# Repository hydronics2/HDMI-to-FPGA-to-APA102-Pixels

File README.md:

# Oregon Museum of Science & Industry (OMSI) - giant LED wall

132 APA102 LED panels, 680 pixels per panel, 90,000 pixels, 300sqft, 4 Spartan 6 Mojo FPGAs
[hackaday.io](https://hackaday.io/project/163657-hdmi-to-fpga-to-apa102)

LED Wall at Oregon Museum of Science & Industry(OMSI): https://photos.app.goo.gl/8hZoa7y9F9Lsg7Md9 (animation credit to [yassi @ openprocessing.org](https://www.openprocessing.org/user/65007))

The creative director wanted to put the LED display behind a wood grain pattern similar to the wall at Microsoft HQ. When the LEDs are off the visitor sees a seemless, unobtrusive wall. To make the LEDs pop behind the wood grain graphic we used a very brigtht APA102.

The resolution is about 24' wide by 14' high. That's 408 pixels wide 220 pixels tall. Not quite VGA.

The FPGA's boards are Spartan 6 on a Mojo development platform: https://alchitry.com/ The wall is broken down into 4 sections for 4 Mojo's and each Mojo receives the same HDMI signal but only grabs pixels for the section of LEDs it controls.

Alchitry has an HDMI shield for the Mojo and the FPGA code is written in their programming environment in Lucid a form of Verilog. It's great for beginners. This was my first FPGA project.

The HDMI signal is decoded and pixels arranged for each panel in local memory (RAM). There is just enough memory to save about 30% of the pixels so it takes 3 passes to arrange and output all the pixels... 60HZ / 3 gives us 20 frames per second. Thanks to [David Hulton](https://www.meetup.com/PNW-FPGA-Hackers-Meetup/) and Devin Boyer for sharing their mad FPGA memory tricks at [Toorcamp 2018](https://toorcamp.toorcon.net/).

The SPI clock speed for writing to the APA102 also has speed limits as we 'race the beam.' Here's a great article by [Paul Stoffregen (teensy)](https://www.pjrc.com/why-apa102-leds-have-trouble-at-24-mhz/) on these limits. The gist is the clock signals start to deteriorate between the pixels. For the 680 LEDs in our panel, I was able to write confidently at 6.25 MHZ. You can see how this clock signal is generated in any one of the 32 SPI modules in the source file under Mojo.

The FPGA generates an SPI clock and data signal to each LED panel. The signals are immediately fed from a simple shield to another custom PCB with [RS485 transmitters](https://www.digikey.com/product-detail/en/texas-instruments/AM26LV31EIDR/296-24690-1-ND/2092512) shown above. The transmitter chips output differential signal pairs that pass easily in ethernet cords over 20-30 feet to each panel location. At the LED panel, the signals are received with [transceiver](https://www.digikey.com/product-detail/en/maxlinear-inc/SP485EN-L-TR/1016-1829-1-ND/3586546) chips bacck into clock and data lines and connected to their respective LED panel. This custom PCB also has a small DC-DC voltage transformers that take a 45VDC buss down to the 5V required for the LEDs.  The below PCB has tranceiver chips and three DC-DC transformers serving 3 LED panels. Thanks to Tom Moxon with [Pattern Agents](http://patternagents.com/) for help designing this circuit.

The led panels themselves are little more than strip LEDs that have been connected together.  We had them customized for our particular geometry by the [supplier](https://www.aliexpress.com/store/product/30-40-pixels-RGB-full-color-WS2812B-Flexible-LED-Pixel-Panel-Light-DC5V/701799_32601735218.html).

Mojo HDMI Shield: https://embeddedmicro.com/products/hdmi-shield

This design builds off of a lucid module example for decoding HDMI signals: https://embeddedmicro.com/blogs/tutorials/hdmi-shield-basics

Thanks to Walsh Construction for making it look easy to hang giant pieces of Acrylic exactly on target.

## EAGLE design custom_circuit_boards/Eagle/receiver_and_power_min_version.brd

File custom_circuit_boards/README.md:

# Custom Circuit Boards

We used 3 types of circuit boards.
* A simple shield for the mojo that broke out all the SPI and Clock signals to the LED panels.
* A transmitter board that sends the clock and data signal out over RS485
* A receiver board that has transceiver chips, takes the signals 

Mojo Shield has all the pins broken out. We needed 33 SPI Data pins and the clock pin was shared across all the Panels.  The pins are broken out to 5.08mm phoenix connectors. The HDMI shield fits on the Mojo and this shield connects ontop of the HDMI shield. [Oshpark](https://oshpark.com/shared_projects/AGi8q5pp)

The transmitter board takes two SPI signals (Clock and Data) and passes the signals through an RS485 transmitter chip. The differential signals are routed to an ethernet jack. This board could have been integrated into the Mojo shield to reduce noise but my disigning, programming, prototyping, and installing timelines compressed the schedule and I had to learn as I went. [Oshpark](https://oshpark.com/shared_projects/nhExJAWv)

* transmitter chip: Texas Instrument AM27LV31 296-24690-1-ND
* RJ45 ethernet jack: 380-1316-5-ND
* 

The receiver board receives RS485 signals via a RJ485 ethernet jack. Converts the two differential pairs back into clock and data SPI signals and connects to one LED panel. The board also has a DC-to-DC converter that takes 45V to 5V to supply to the LED panel. I did not put the TVS protection diodes on the boards but added them on just the last few boards I made when troubleshooting noise issues.  Also, in addition to the 120ohm termination resistors on the RS485 bus, the original boards have 4.7k pullup and pulldown resistors on the bus. Modern RS485 chips have whats called "failsafe" against idle(no Data) conditions that these resistors are meant to deter.... so I left them out of these last few single signal boards shown here. [Oshpark](https://oshpark.com/shared_projects/qSwC1Fum)

* Trnsceiver Chip: SP485EN, 1016-1829-1-ND
* RJ45 Ethernet Jack: 380-1316-5-ND
* DC-DC converter - PYB20-Q48-S5

* [Mojo Development Board](https://alchitry.com/products/mojo-v3)
* [HDMI Shield](https://alchitry.com/products/hdmi-shield)
* [RS485 transmitter chips](https://www.digikey.com/product-detail/en/texas-instruments/AM26LV31EIDR/296-24690-1-ND/2092512) shown above.
* [RS485 transceiver chips](https://www.digikey.com/product-detail/en/maxlinear-inc/SP485EN-L-TR/1016-1829-1-ND/3586546) chips
* [Mojo HDMI Shield](https://embeddedmicro.com/products/hdmi-shield)

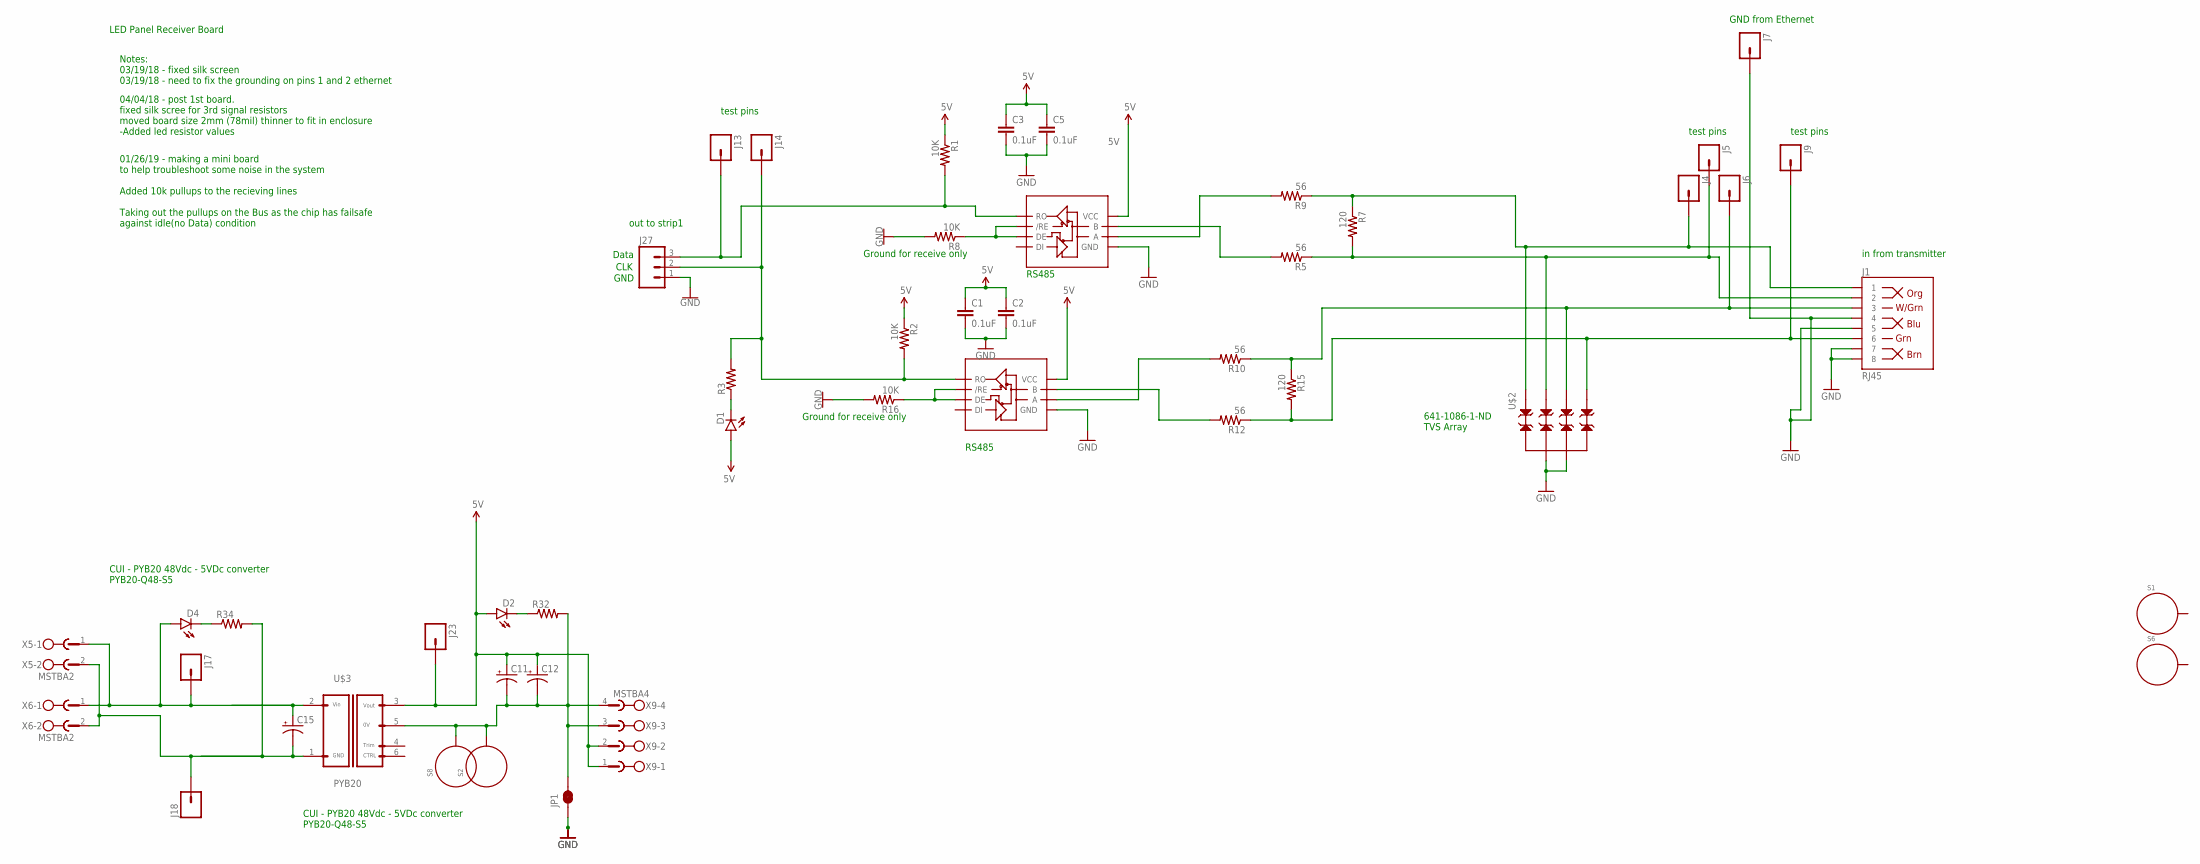
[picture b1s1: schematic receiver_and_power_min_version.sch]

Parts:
C1, C2, C3, C5: 0.1uF; 0805
C11, C12, C15: CAP_POLPTH4; CPOL-RADIAL-1000UF-25V
D1, D2, D4: LED3MM
J1: RJ45; RJ45-8
J4, J5, J6, J7, J9, J13, J14, J17, J18, J23: M01PTH; 1X01
J27: M03SCREW; SCREWTERMINAL-3.5MM-3
JP1: JUMPER-PAD-2-NC_BY_TRACE; PAD-JUMPER-2-NC_BY_TRACE_YES_SILK
R1, R2, R8, R16: 10K; 0805
R3: RESISTOR0805-RES; 0805
R5, R9, R10, R12: 56; 0805
R7, R15: 120; 0805
R32, R34: RESISTORPTH-1/4W; AXIAL-0.4
S1, S2, S6, S8: STANDOFF_ELECTRICAL5-32; STANDOFF_ELECTRICAL_5_32
U1, U2: ST1480ACSOIC; SO08
U$2: TVS_ARRAY; SOT26
U$3: PYB20; CUI_PYB20_PCB_DC_DC
X5, X6: MSTBA2
X9: MSTBA4

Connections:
5GND1: C11.2 (-), C12.2 (-), JP1.2, R32.P$2 (2), S2.P1, S8.P1, U$3.5 (0V), X9.3, X9.4
5V: C1.1, C2.1, C3.1, C5.1, C11.1 (+), C12.1 (+), D1.A, D2.A, J23.1, R1.1, R2.1, U1.8 (VCC), U2.8 (VCC), U$3.3 (V+), X9.1, X9.2
48GND: C15.-, J18.1, R34.P$2 (2), U$3.1 (GND1), X5.2, X6.2
48V: C15.+, D4.A, J17.1, U$3.2 (VIN), X5.1, X6.1
A: R9.2, U1.6 (A)
A1: R10.2, U2.6 (A)
AO: J1.1, J4.1, R7.1, R9.1, U$2.1
AO1: J1.3, J6.1, R10.1, R15.1, U$2.4
B: R5.2, U1.7 (B)
B1: R12.2, U2.7 (B)
BO: J1.2, J5.1, R5.1, R7.2, U$2.3
BO1: J1.6, J9.1, R12.1, R15.2, U$2.6
DE: R8.1, U1.2 (/RE), U1.3 (DE)
DE1: R16.1, U2.2 (/RE), U2.3 (DE)
GND: C1.2, C2.2, C3.2, C5.2, J1.4, J1.5, J1.7, J1.8, J7.1, J27.1, JP1.1, R8.2, R16.2, U1.5 (GND), U2.5 (GND), U$2.2, U$2.5
unnamed: D1.K (C), R3.1
unnamed: D4.K (C), R34.P$1 (1)
unnamed: D2.K (C), R32.P$1 (1)
RXD: J13.1, J27.3, R1.2, U1.1 (RO)
RXD1: J14.1, J27.2, R2.2, R3.2, U2.1 (RO)

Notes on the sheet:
in from transmitter
test pins
Ground for receive only
out to strip1
LED Panel Receiver Board
GND from Ethernet
RS485
Notes: 03/19/18 - fixed silk screen 03/19/18 - need to fix the grounding on pins 1 and 2 ethernet
GND
CLK
Data
CUI - PYB20 48Vdc - 5VDc converter PYB20-Q48-S5
04/04/18 - post 1st board. fixed silk scree for 3rd signal resistors moved board size 2mm (78mil) thinner to fit in enclosure -Added led resistor values
01/26/19 - making a mini board to help troubleshoot some noise in the system Added 10k pullups to the recieving lines Taking out the pullups on the Bus as the chip has failsafe against idle(no Data) condition
641-1086-1-ND TVS Array

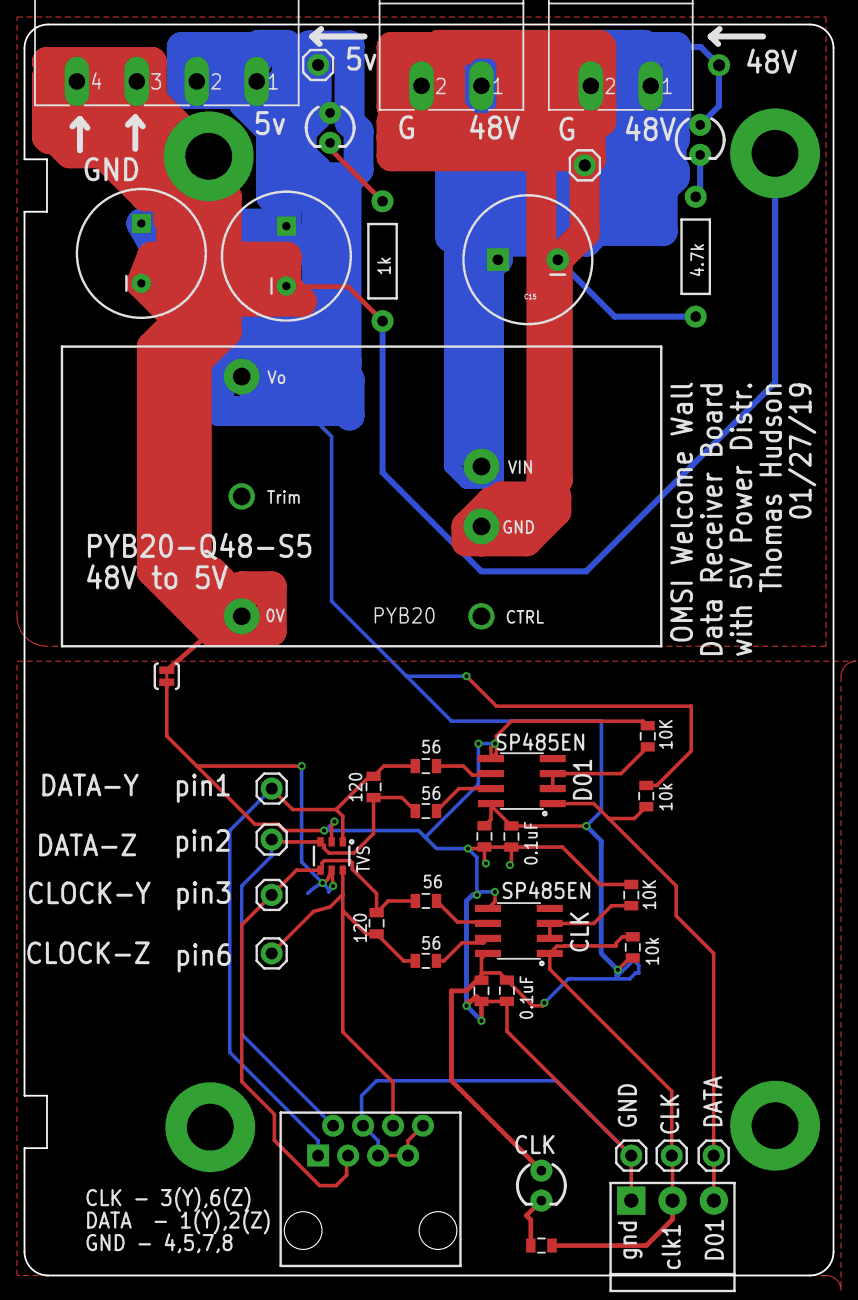
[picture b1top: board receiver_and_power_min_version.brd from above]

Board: 2 copper layers, 68.6 x 106.0 mm, 47 parts (1 on the bottom side), 20 nets.

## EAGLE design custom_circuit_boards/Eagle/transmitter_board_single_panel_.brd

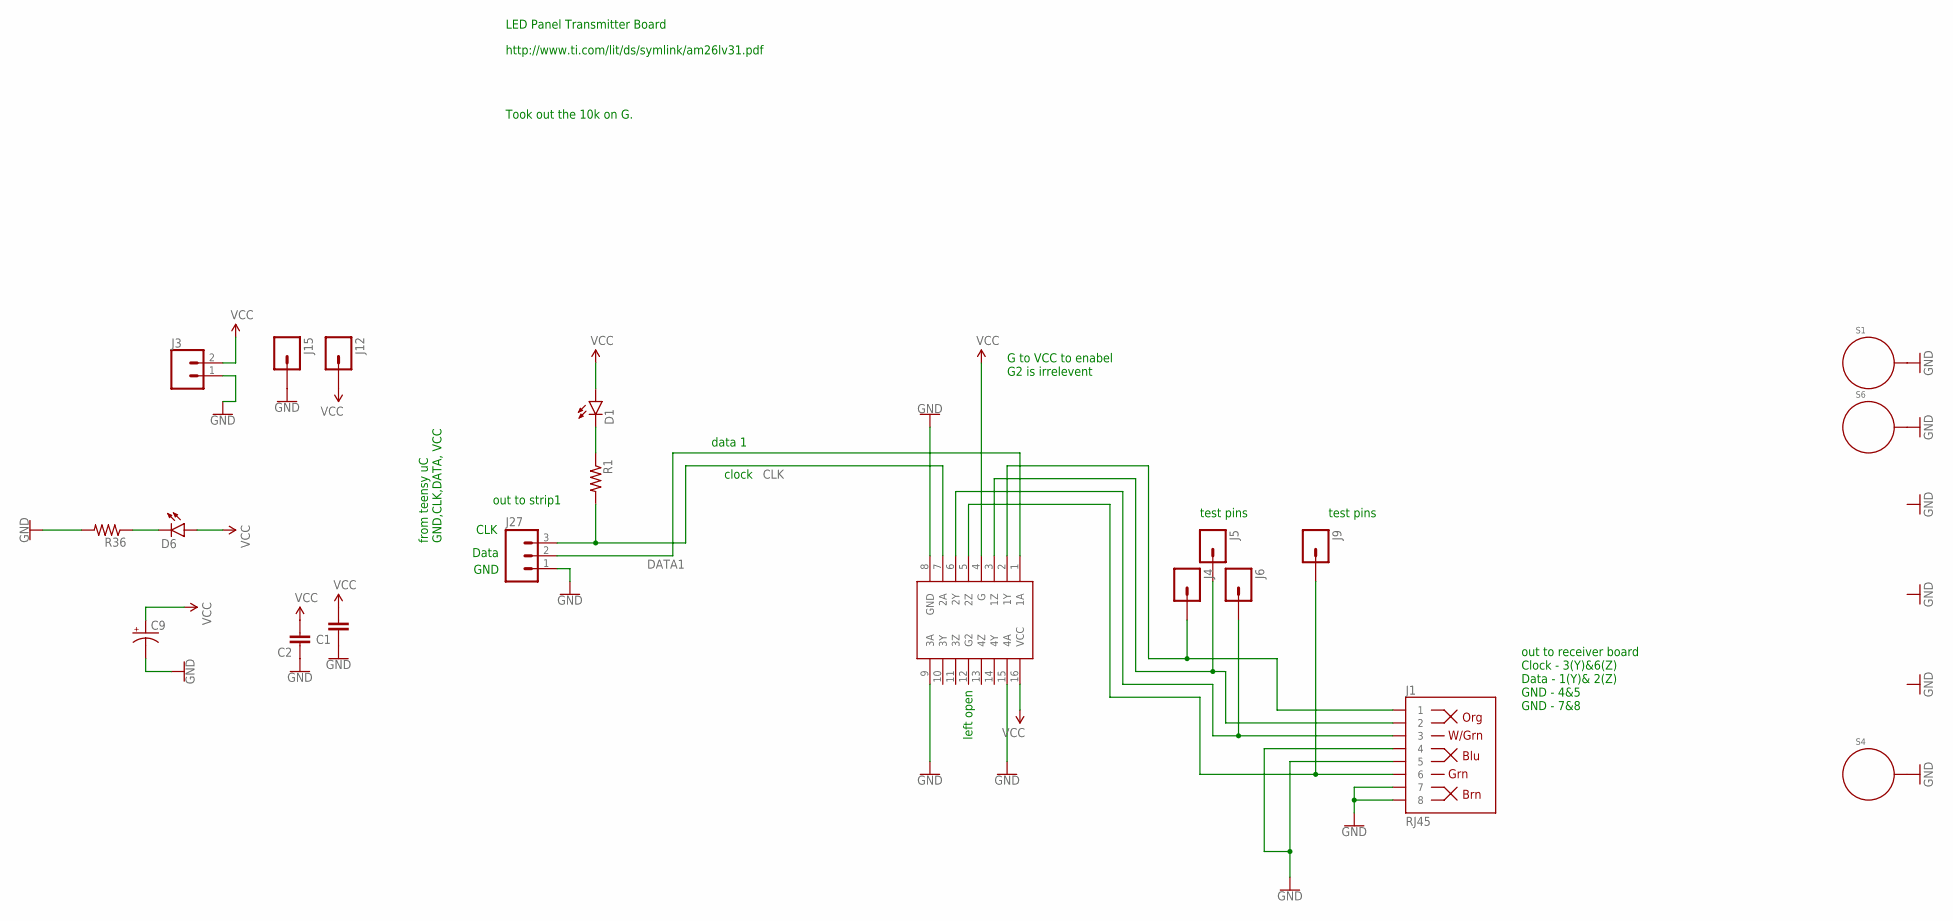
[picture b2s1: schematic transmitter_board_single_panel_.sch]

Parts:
C1, C2: CAP0805; 0805
C9: CAP_POLPTH1; CPOL-RADIAL-100UF-25V
D1, D6: LED3MM
J1: RJ45; RJ45-8
J3: CONN_025MM; SCREWTERMINAL-5MM-2
J4, J5, J6, J9, J12, J15: M01PTH; 1X01
J27: M03SCREW; SCREWTERMINAL-3.5MM-3
R1, R36: RESISTOR0805-RES; 0805
S1, S4, S6: STANDOFF_ELECTRICAL5-32; STANDOFF_ELECTRICAL_5_32
U$1: AM26LV31_QUAD_LINE_DRIVER; SO016

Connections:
CLK: J27.3, R1.2, U$1.7 (2A)
DATA1: J27.2, U$1.1 (1A)
GND: C1.1, C2.1, C9.2 (-), J1.4, J1.5, J1.7, J1.8, J3.1, J15.1, J27.1, R36.2, S1.P1, S4.P1, S6.P1, U$1.8 (GND), U$1.9 (3A), U$1.15 (4A)
unnamed: J1.1, J4.1, U$1.2 (1Y)
unnamed: J1.2, J5.1, U$1.3 (1Z)
unnamed: J1.3, J6.1, U$1.6 (2Y)
unnamed: J1.6, J9.1, U$1.5 (2Z)
unnamed: D1.K (C), R1.1
unnamed: D6.K (C), R36.1
VCC: C1.2, C2.2, C9.1 (+), D1.A, D6.A, J3.2, J12.1, U$1.4 (G), U$1.16 (VCC)

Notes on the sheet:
out to receiver board Clock - 3(Y)&6(Z) Data - 1(Y)& 2(Z) GND - 4&5 GND - 7&8
test pins
from teensy uC GND,CLK,DATA, VCC
LED Panel Transmitter Board
data 1
clock
http://www.ti.com/lit/ds/symlink/am26lv31.pdf
G to VCC to enabel G2 is irrelevent
left open
Took out the 10k on G.
out to strip1
GND
CLK
Data

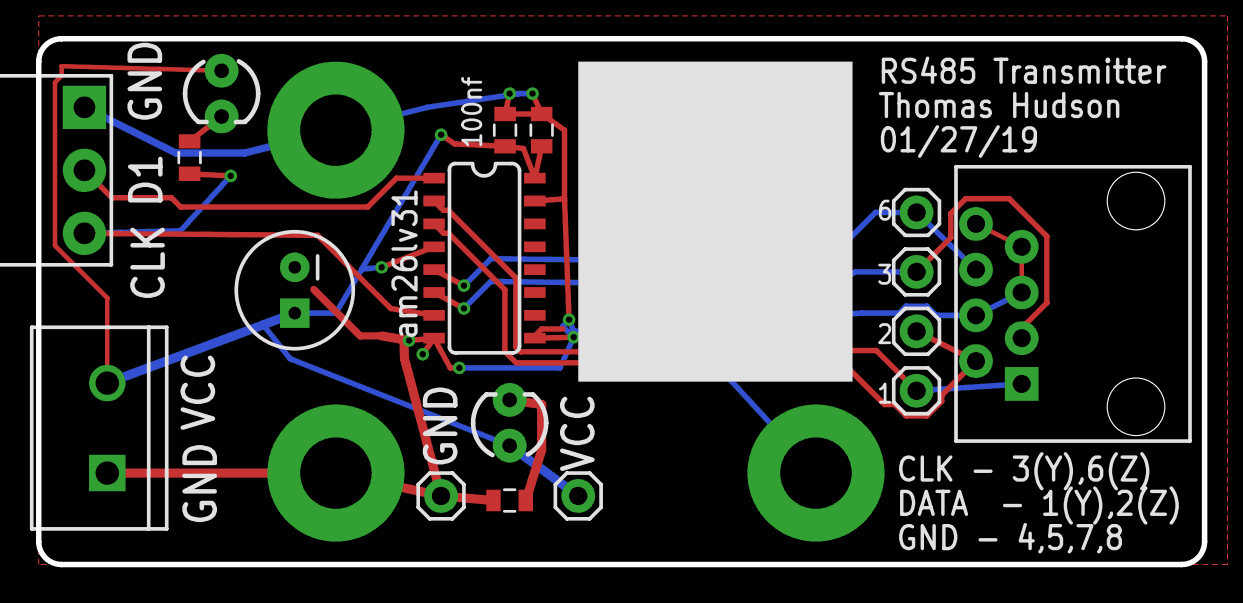
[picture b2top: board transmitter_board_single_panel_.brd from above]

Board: 2 copper layers, 64.8 x 29.2 mm, 20 parts (0 on the bottom side), 10 nets.

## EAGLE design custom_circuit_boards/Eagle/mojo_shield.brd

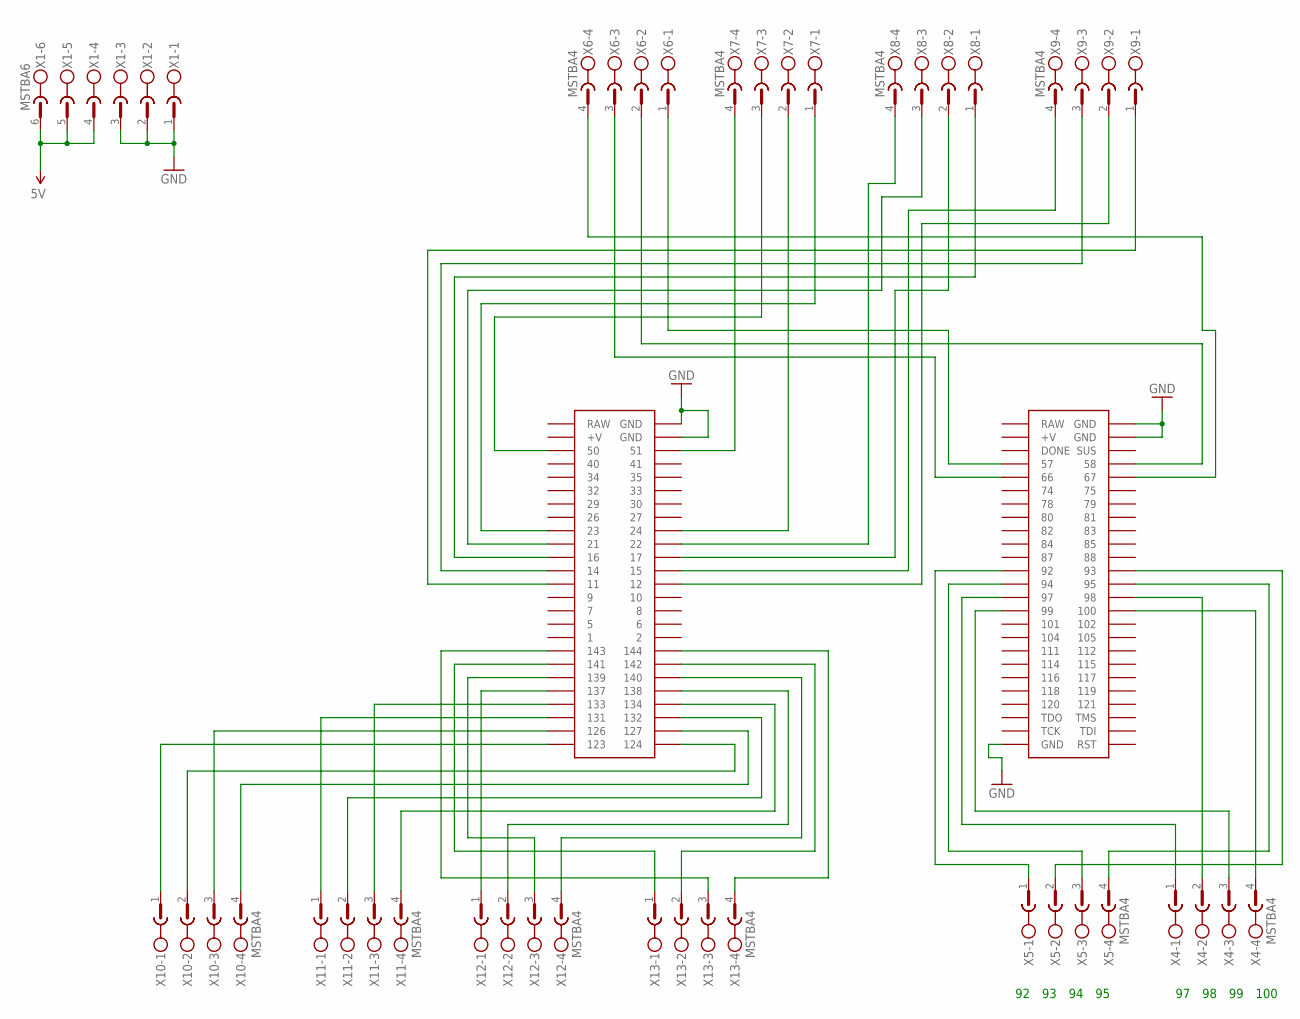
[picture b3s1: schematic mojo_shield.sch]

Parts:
U$1: MOJO_V2V3_NO_LABEL; MOJO_V3_NO_LABEL
X1: MSTBA6
X4, X5, X6, X7, X8, X9, X10, X11, X12, X13: MSTBA4

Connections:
5V: X1.4, X1.5, X1.6
+V: U$1.V@1 (+V), U$1.V@2 (+V)
AREF: U$1.AREF
GND: U$1.GND@1 (GND), U$1.GND@2 (GND), U$1.GND@3 (GND), U$1.GND@4 (GND), U$1.GND@5 (GND), U$1.GND@6 (GND), X1.1, X1.2, X1.3
unnamed: U$1.50, X7.3
unnamed: U$1.51, X7.4
unnamed: U$1.23, X7.1
unnamed: U$1.24, X7.2
unnamed: U$1.11, X9.1
unnamed: U$1.12, X9.2
unnamed: U$1.15, X9.4
unnamed: U$1.17, X8.2
unnamed: U$1.22, X8.4
unnamed: U$1.21, X8.3
unnamed: U$1.16, X8.1
unnamed: U$1.14, X9.3
unnamed: U$1.133, X11.3
unnamed: U$1.134, X11.4
unnamed: U$1.123, X10.1
unnamed: U$1.124, X10.2
unnamed: U$1.99, X4.3
unnamed: U$1.100, X4.4
unnamed: U$1.92, X5.1
unnamed: U$1.93, X5.2
unnamed: U$1.66, X6.3
unnamed: U$1.57, X6.1
unnamed: U$1.58, X6.2
unnamed: U$1.67, X6.4
unnamed: U$1.94, X5.3
unnamed: U$1.97, X4.1
unnamed: U$1.95, X5.4
unnamed: U$1.98, X4.2
unnamed: U$1.132, X11.2
unnamed: U$1.127, X10.4
unnamed: U$1.131, X11.1
unnamed: U$1.126, X10.3
unnamed: U$1.137, X12.1
unnamed: U$1.138, X12.2
unnamed: U$1.144, X13.4
unnamed: U$1.142, X13.2
unnamed: U$1.140, X12.4
unnamed: U$1.143, X13.3
unnamed: U$1.141, X13.1
unnamed: U$1.139, X12.3
RAW: U$1.RAW@1 (RAW), U$1.RAW@2 (RAW)

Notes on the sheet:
100

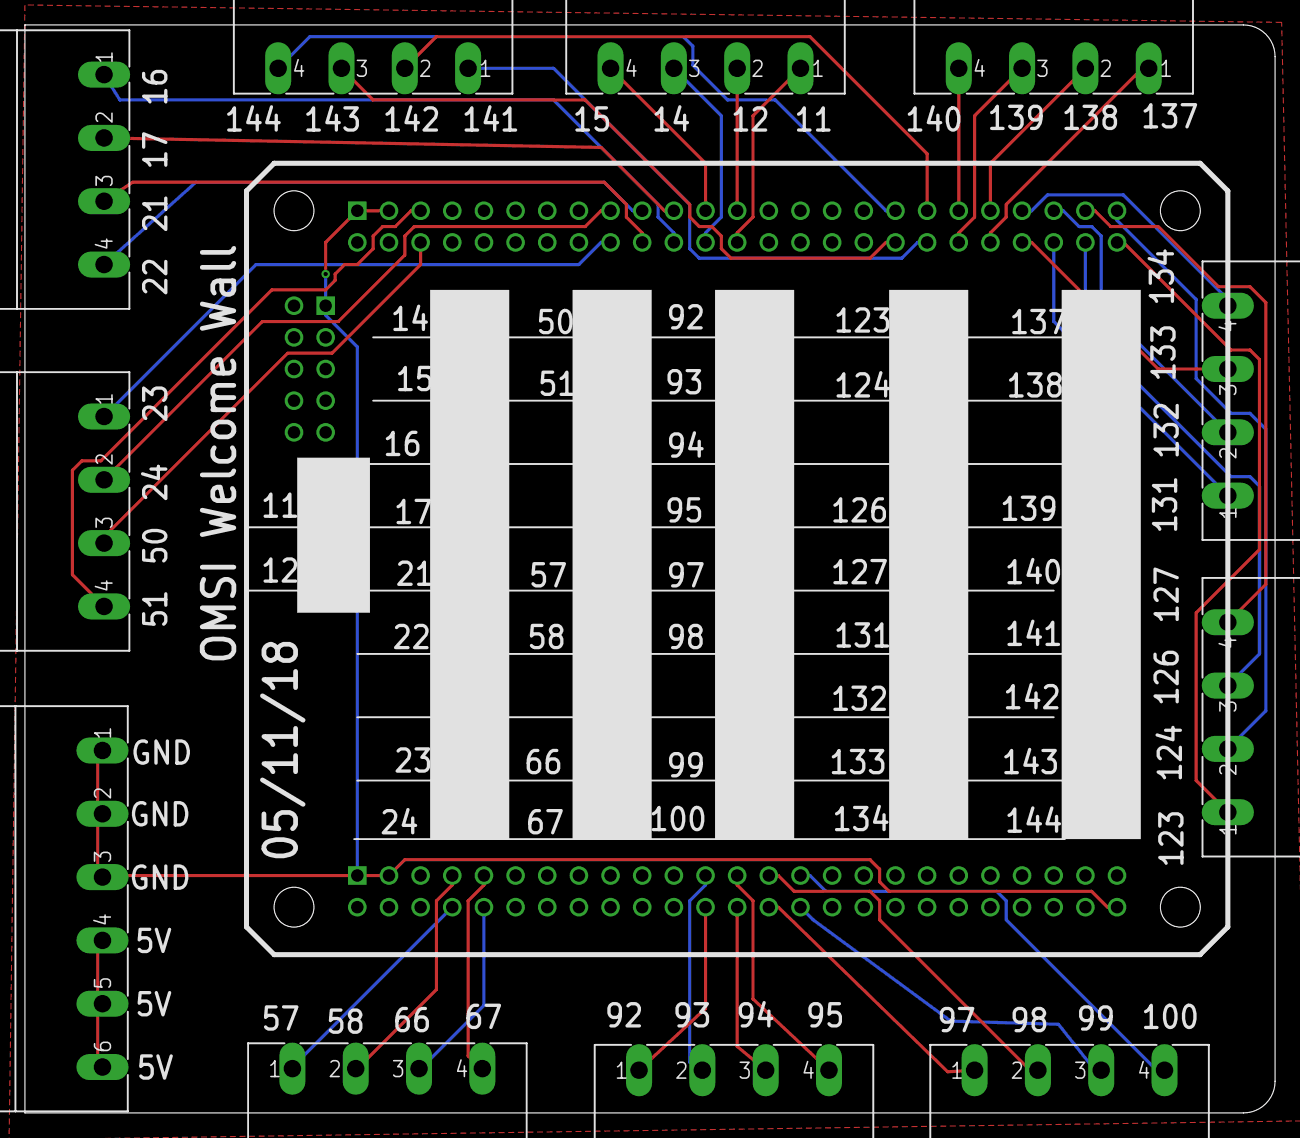
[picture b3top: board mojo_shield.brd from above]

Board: 2 copper layers, 100.3 x 87.3 mm, 12 parts (0 on the bottom side), 44 nets.

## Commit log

2018-06-15 added panels to a total of 6. all bottom left data feed
2018-06-20 added contraint file for led strip pins
2018-07-05 top row working with new spi speed and at 150mhz clock
2018-07-05 added pixel counter and 3 more rows not writing yet...
2018-07-06 6 panels seem to be writing well
2018-07-06 6 panels writing.. the middle panels if each row is flickering.. at the bottom. look slike spi
2018-07-07 130mhz seems the best so far... - trying 130mhz again... 35,000 pixels at end of writing... ... just a little right/left glitch on right panels (top and bottom) // - 130mhz seems the best so far...
2018-07-07 writing top and bottom rows.. changed number from 0,1,2.... 30,21,32 from top to bottom..
2018-07-08 writing 3 similar rows.. 9 panels total...
2018-07-10 scripts for 12 panels but only 6 in active code.. working well...
2018-07-10 15 panels... 12 panels programmed and working..
2018-07-13 fixed frame 5 skipping... Signed-off-by: hydronics2 <hydronics@gmail.com>
2018-07-18 added 4 total frame buffers => 12 simple ram modules for 12 panels
2020-05-25 formatting
2020-05-25 added video
2020-05-25 added pic
2020-05-25 added pics

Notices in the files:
parts and their libraries:
SparkFun-Aesthetics: Licensing: Creative Commons ShareAlike 4.0 International - https://creativecommons.org/licenses/by-sa/4.0
PatternAgents-ProtoPads: License : http://creativecommons.org/licenses/by-sa/4.0
(Creative Commons 4.0)
